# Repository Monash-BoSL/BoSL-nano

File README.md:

# micro-BoSL
A micro version of the BoSL board

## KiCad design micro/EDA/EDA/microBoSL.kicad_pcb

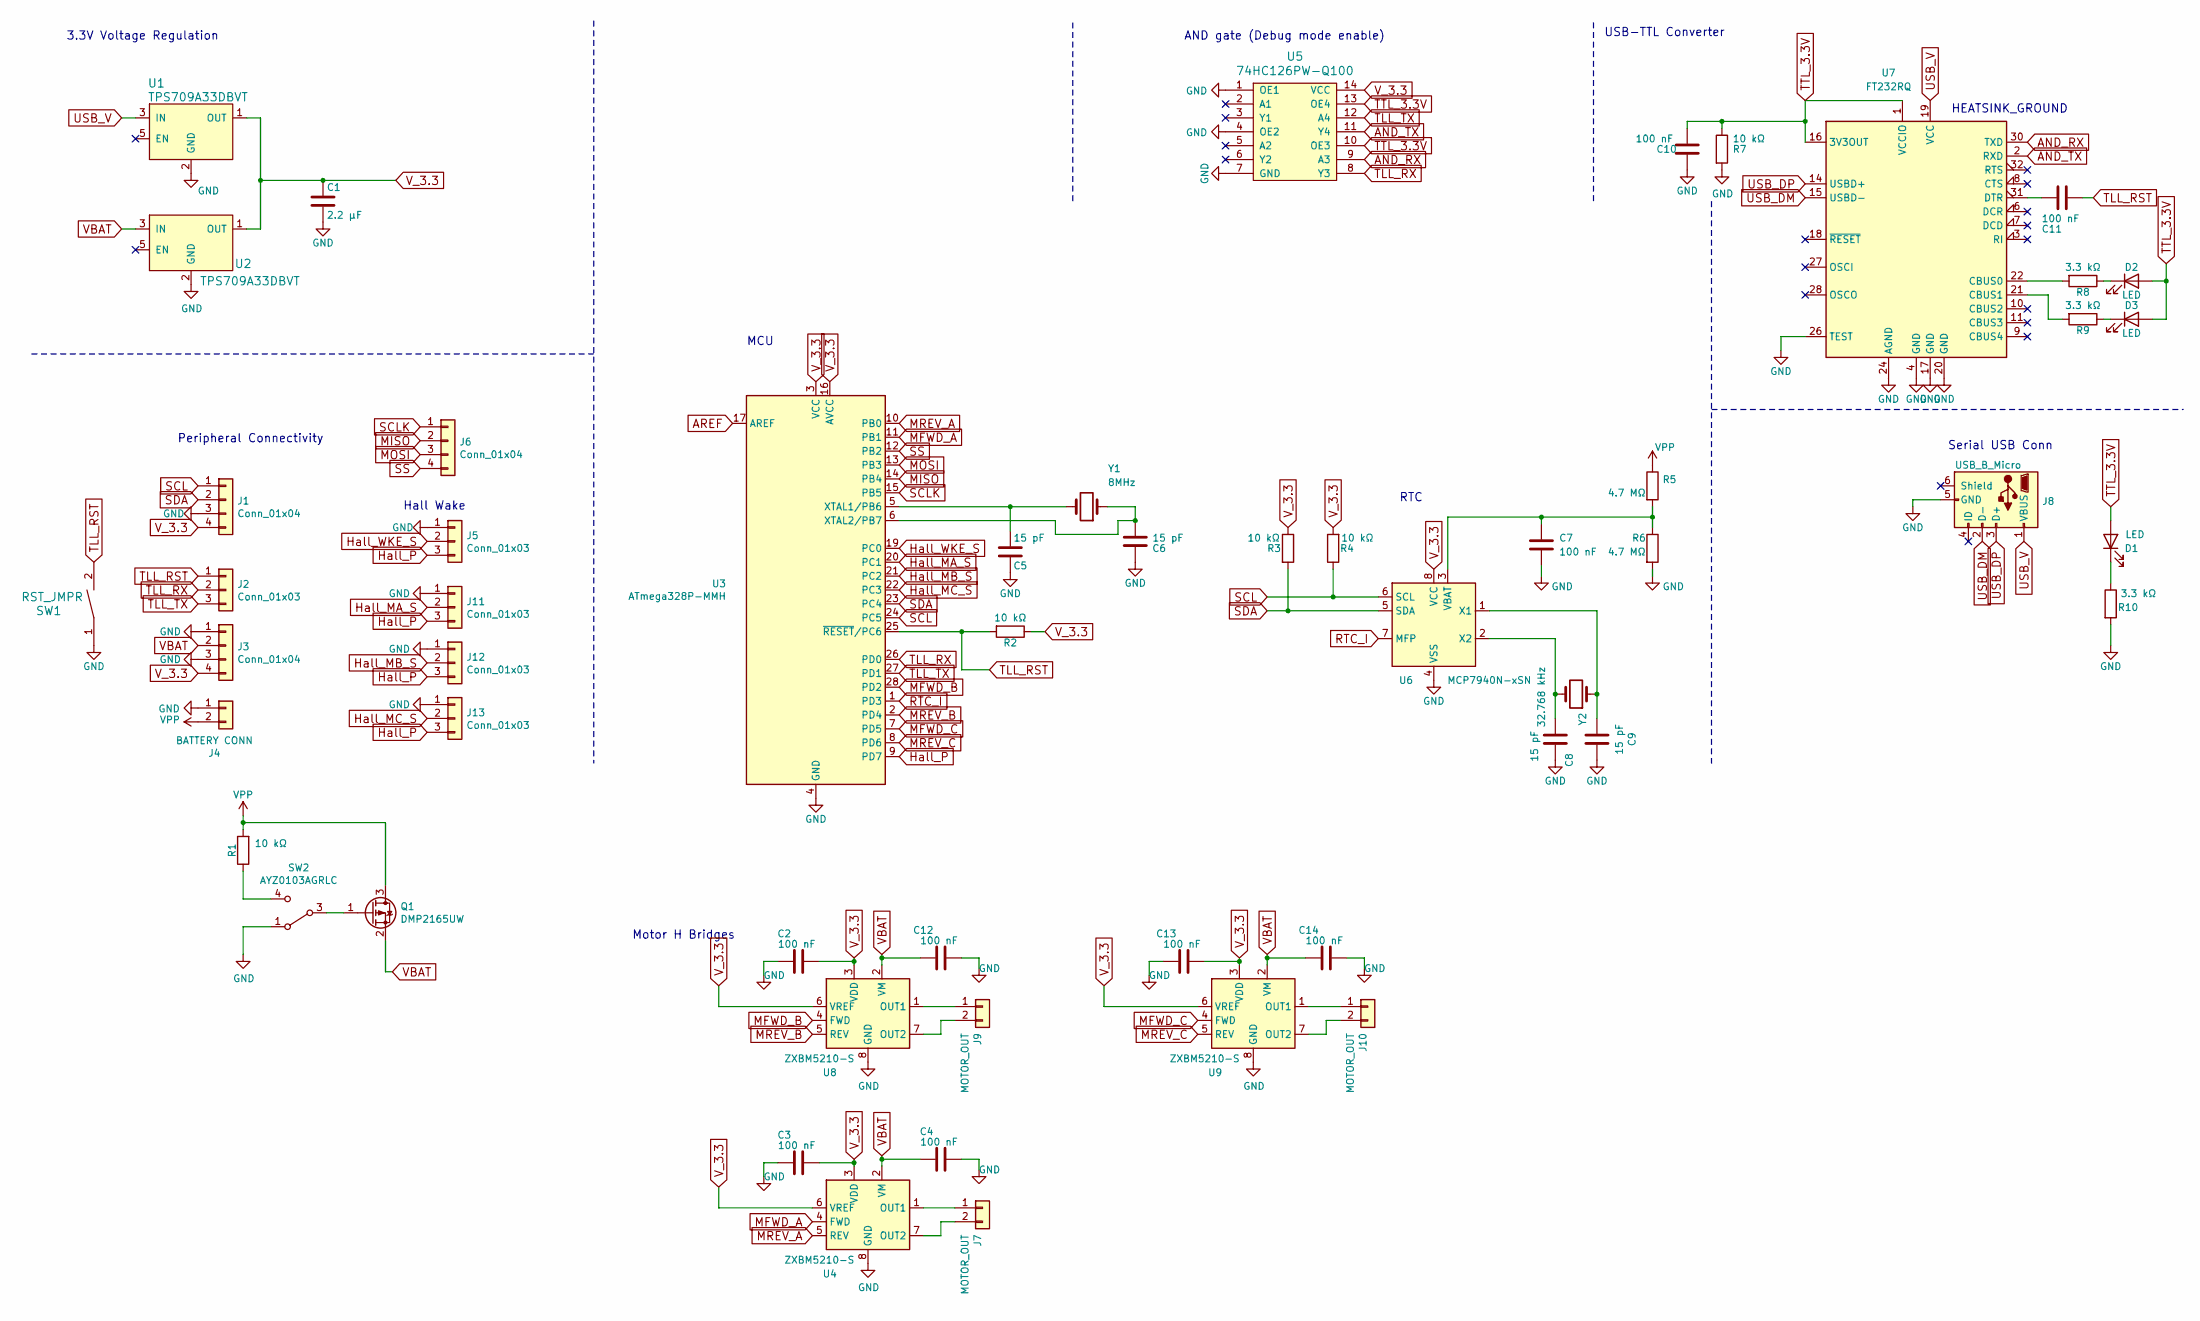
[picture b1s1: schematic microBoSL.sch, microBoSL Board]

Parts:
C1: 2.2 μF; C_0805_2012Metric
C2, C3, C4, C7, C10, C11, C12, C13, C14: 100 nF; C_0402_1005Metric
C5, C6, C8, C9: 15 pF; C_0402_1005Metric
D1, D2, D3: LED; LED_0603_1608Metric
J1, J6: Conn_01x04; PinHeader_1x04_P1.27mm_Vertical
J2: Conn_01x03; PinHeader_1x03_P1.27mm_Vertical
J3: Conn_01x04; PinHeader_1x04_P2.54mm_Vertical
J4: BATTERY CONN; PinHeader_1x02_P2.54mm_Vertical
J5, J11, J12, J13: Conn_01x03; PinHeader_1x03_P2.00mm_Vertical
J7, J9, J10: MOTOR_OUT; PinHeader_1x02_P2.54mm_Vertical
J8: USB_B_Micro; USB_Micro-B_Molex-105133-0001
Q1: DMP2165UW; SOT-323_SC-70
R1, R2, R3, R4, R7: 10 kΩ; R_0402_1005Metric
R5, R6: 4.7 MΩ; C_0402_1005Metric
R8, R9, R10: 3.3 kΩ; R_0402_1005Metric
SW1: RST_JMPR; SolderJumper-2_P1.3mm_Open_RoundedPad1.0x1.5mm
SW2: AYZ0103AGRLC
U1, U2: TPS709A33DBVT; SOT-23-5
U3: ATmega328P-MMH; QFN-28-1EP_4x4mm_P0.45mm_EP2.4x2.4mm
U4, U8, U9: ZXBM5210-S; SOIC-8_3.9x4.9mm_P1.27mm
U5: 74HC126PW-Q100; TSSOP-14_4.4x5mm_P0.65mm
U6: MCP7940N-xSN; DFN-8-1EP_3x2mm_P0.5mm_EP1.3x1.5mm
U7: FT232RQ; QFN-32-1EP_5x5mm_P0.5mm_EP3.1x3.1mm
Y1: 8MHz; Crystal_SMD_5032-2Pin_5.0x3.2mm
Y2: 32.768 kHz; Crystal_SMD_2012-2Pin_2.0x1.2mm

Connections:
AND_RX: U5.9 (A3), U7.30 (TXD)
AND_TX: U5.11 (Y4), U7.2 (RXD)
AREF: U3.17 (AREF)
GND: C1.2, C2.1, C3.1, C4.2, C5.1, C6.1, C7.2, C8.1, C9.1, C10.2, C12.2, C13.1, C14.2, J1.3, J3.1, J3.3, J4.1, J5.1, J8.5 (GND), J11.1, J12.1, J13.1, R6.2, R7.2, R10.2, SW1.1, SW2.1 (A), U1.2 (GND), U2.2 (GND), U3.4 (GND), U3.18 (GND), U3.29 (GND), U4.8 (GND), U5.1 (OE1), U5.4 (OE2), U5.7 (GND), U6.4 (VSS), U7.4 (GND), U7.17 (GND), U7.20 (GND), U7.24 (AGND), U7.26 (TEST), U7.33, U8.8 (GND), U9.8 (GND); also elsewhere on the board
Hall_MA_S: J11.2, U3.20 (PC1)
Hall_MB_S: J12.2, U3.21 (PC2)
Hall_MC_S: J13.2, U3.22 (PC3)
Hall_P: J5.3, J11.3, J12.3, J13.3, U3.9 (PD7)
Hall_WKE_S: J5.2, U3.19 (PC0)
MFWD_A: U3.11 (PB1), U4.4 (FWD)
MFWD_B: U3.28 (PD2), U8.4 (FWD)
MFWD_C: U3.7 (PD5), U9.4 (FWD)
MISO: J6.2, U3.14 (PB4)
MOSI: J6.3, U3.13 (PB3)
MREV_A: U3.10 (PB0), U4.5 (REV)
MREV_B: U3.2 (PD4), U8.5 (REV)
MREV_C: U3.8 (PD6), U9.5 (REV)
unnamed: C5.2, U3.5 (XTAL1/PB6), Y1.2
unnamed: C6.2, U3.6 (XTAL2/PB7), Y1.1
unnamed: C7.1, R5.2, R6.1, U6.3 (VBAT)
unnamed: C8.2, U6.2 (X2), Y2.2
unnamed: C9.2, U6.1 (X1), Y2.1
unnamed: C11.2, U7.31 (DTR)
unnamed: D1.1 (K), R10.1
unnamed: D2.1 (K), R8.1
unnamed: D3.1 (K), R9.1
unnamed: J7.1, U4.1 (OUT1)
unnamed: J7.2, U4.7 (OUT2)
unnamed: J9.1, U8.1 (OUT1)
unnamed: J9.2, U8.7 (OUT2)
unnamed: J10.1, U9.1 (OUT1)
unnamed: J10.2, U9.7 (OUT2)
unnamed: Q1.1 (G), SW2.3 (B)
unnamed: R1.1, SW2.4 (C)
unnamed: R8.2, U7.22 (CBUS0)
unnamed: R9.2, U7.21 (CBUS1)
RTC_I: U3.1 (PD3), U6.7 (MFP)
SCL: J1.1, R4.1, U3.24 (PC5), U6.6 (SCL)
SCLK: J6.1, U3.15 (PB5)
SDA: J1.2, R3.2, U3.23 (PC4), U6.5 (SDA)
SS: J6.4, U3.12 (PB2)
TLL_RST: C11.1, J2.1, R2.2, SW1.2, U3.25 (~RESET~/PC6); also elsewhere on the board
TLL_RX: J2.2, U3.26 (PD0), U5.8 (Y3)
TLL_TX: J2.3, U3.27 (PD1), U5.12 (A4)
TTL_3.3V: C10.1, D1.2 (A), D2.2 (A), D3.2 (A), R7.1, U5.10 (OE3), U5.13 (OE4), U7.1 (VCCIO), U7.16 (3V3OUT)
USB_DM: J8.2 (D-), U7.15 (USBD-)
USB_DP: J8.3 (D+), U7.14 (USBD+)
USB_V: J8.1 (VBUS), U1.3 (IN), U7.19 (VCC)
VBAT: C4.1, C12.1, C14.1, J3.2, Q1.2 (S), U2.3 (IN), U4.2 (VM), U8.2 (VM), U9.2 (VM)
VPP: J4.2, Q1.3 (D), R1.2, R5.1
V_3.3: C1.1, C2.2, C3.2, C13.2, J1.4, J3.4, R2.1, R3.1, R4.2, U1.1 (OUT), U2.1 (OUT), U3.3 (VCC), U3.16 (AVCC), U4.3 (VDD), U4.6 (VREF), U5.14 (VCC), U6.8 (VCC), U8.3 (VDD), U8.6 (VREF), U9.3 (VDD), U9.6 (VREF)

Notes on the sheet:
3.3V Voltage Regulation
Peripheral Connectivity
RTC
Hall Wake
HEATSINK_GROUND
USB-TTL Converter
AND gate (Debug mode enable)
Serial USB Conn
MCU
Motor H Bridges

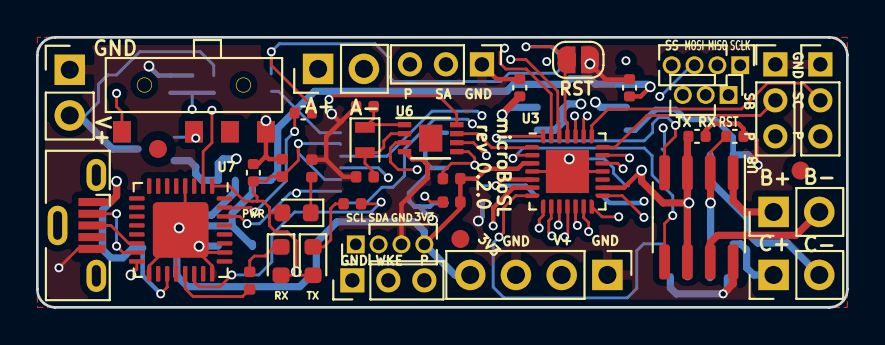
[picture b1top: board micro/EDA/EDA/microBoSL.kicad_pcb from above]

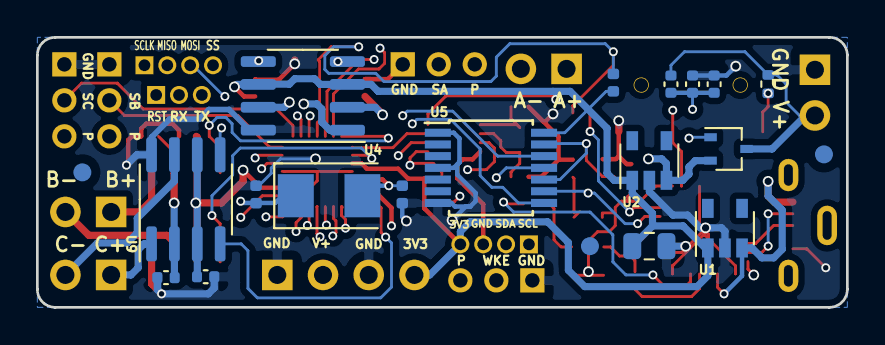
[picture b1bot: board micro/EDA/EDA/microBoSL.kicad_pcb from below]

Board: 4 copper layers, 45.0 x 15.0 mm, 54 parts (17 on the bottom side), 50 nets.

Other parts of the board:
RST: RST_JMPR; SolderJumper-2_P1.3mm_Open_RoundedPad1.0x1.5mm

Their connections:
GND: RST.1; also elsewhere on the board
TLL_RST: RST.2; also elsewhere on the board

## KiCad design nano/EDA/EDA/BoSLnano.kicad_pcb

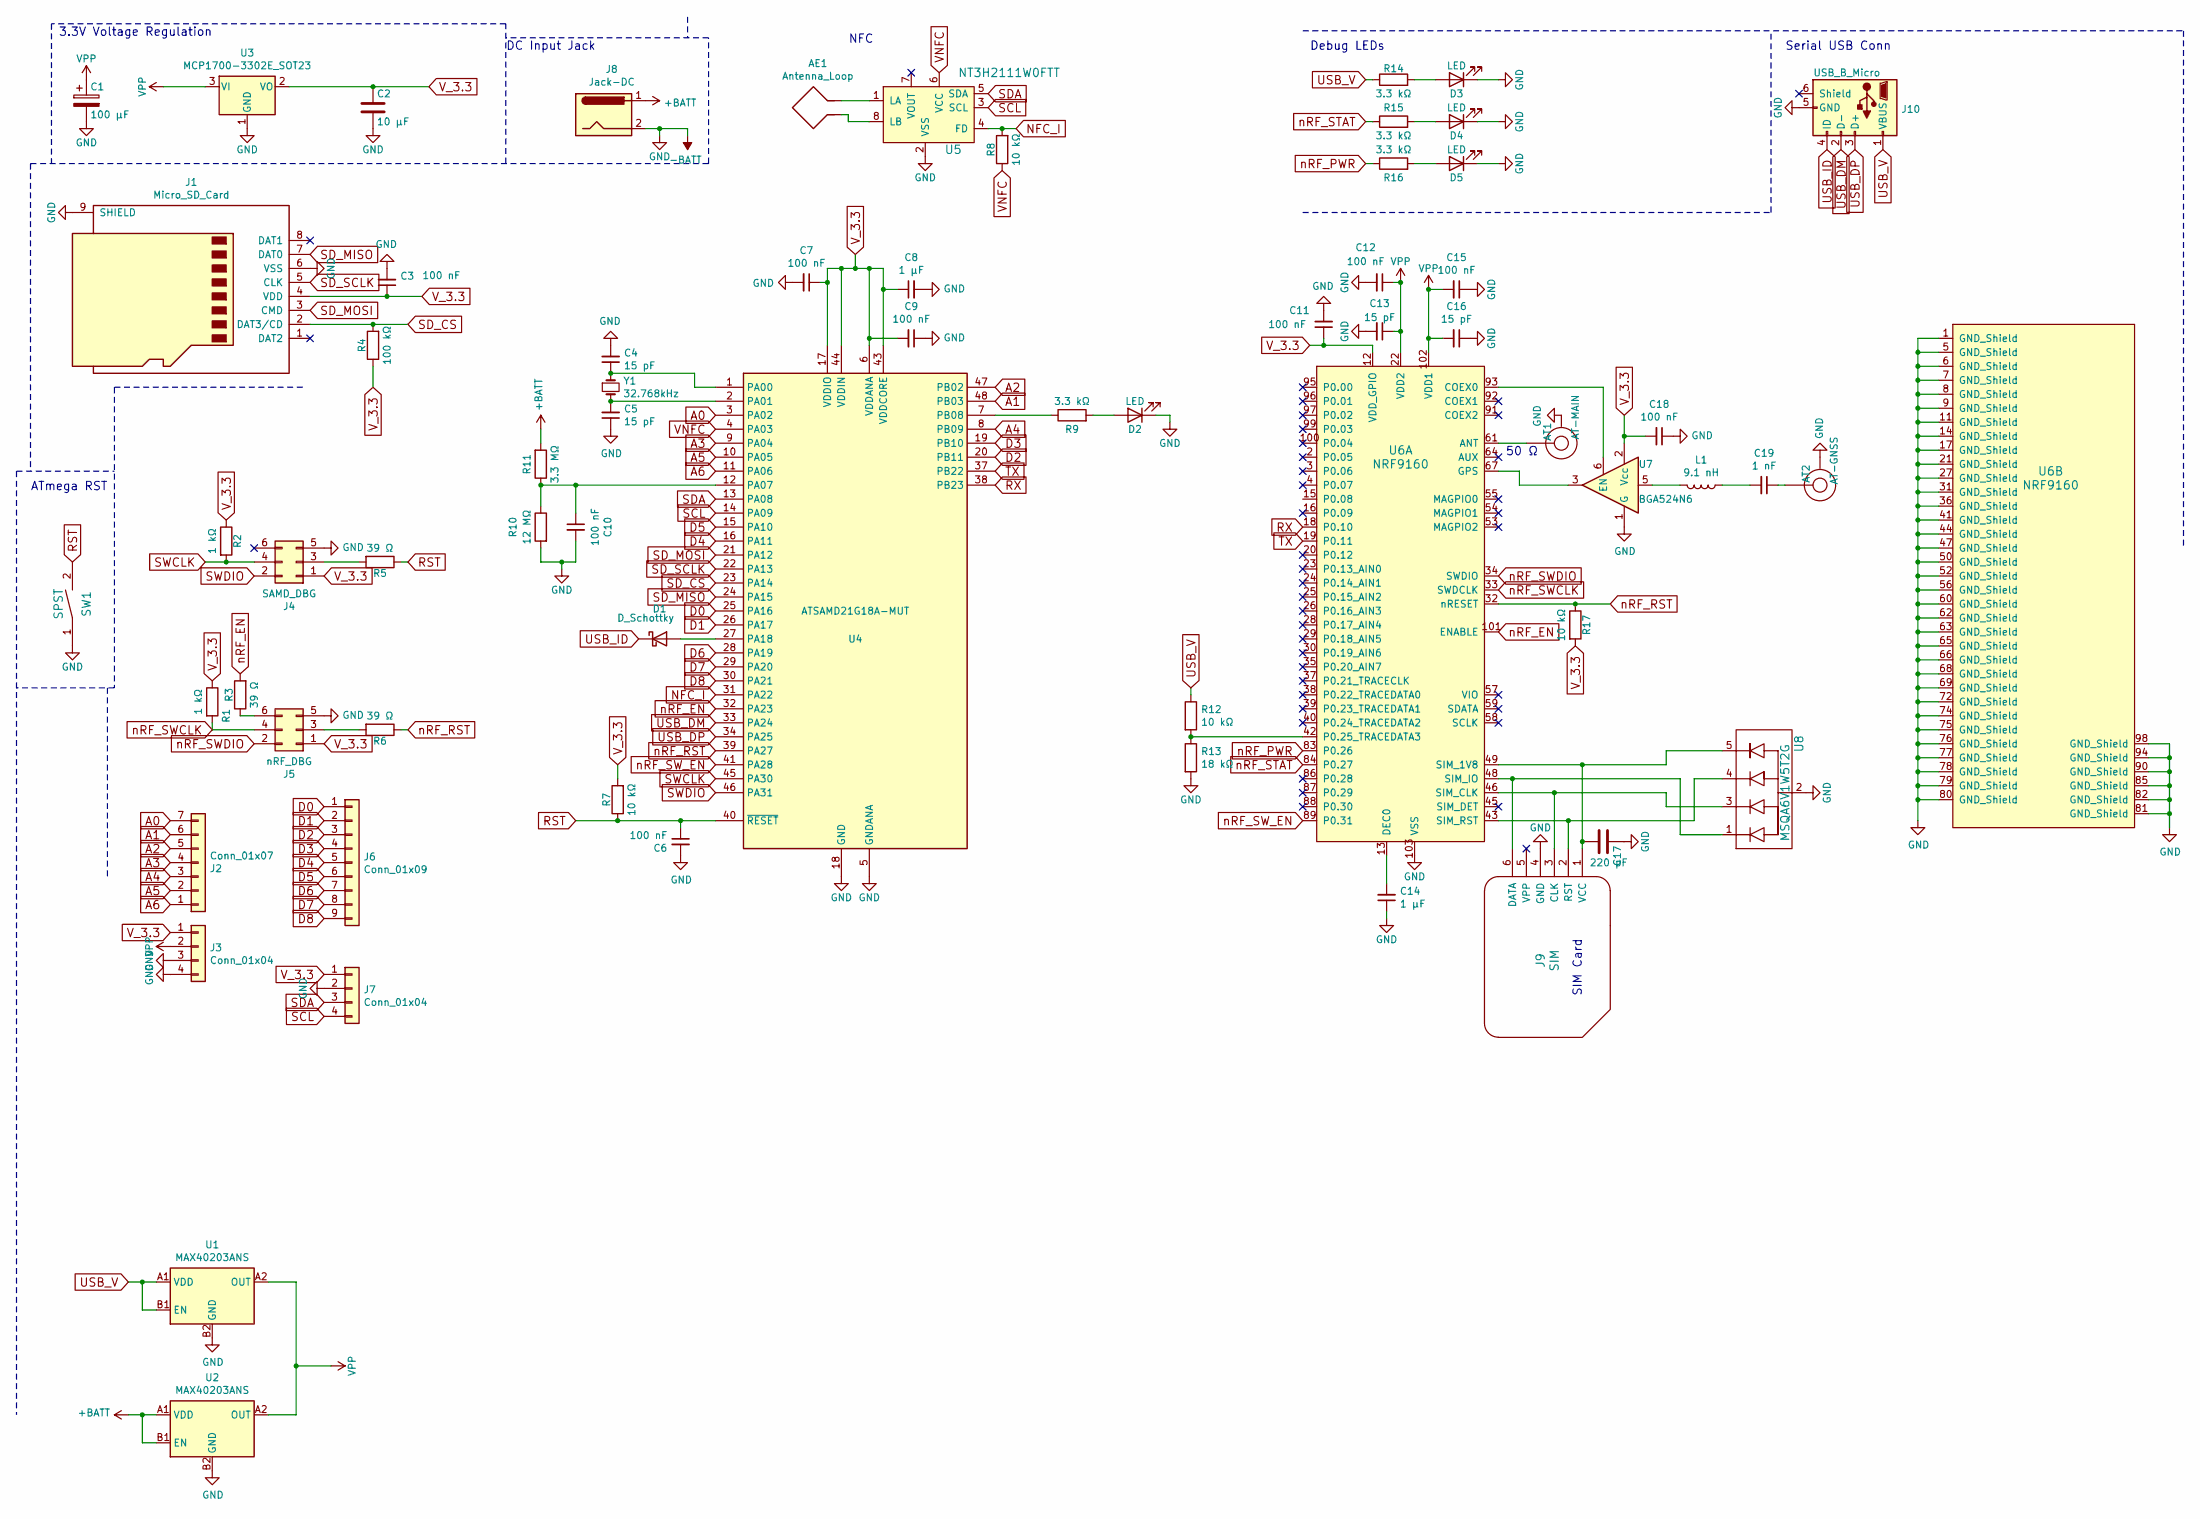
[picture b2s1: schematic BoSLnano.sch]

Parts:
AE1: Antenna_Loop; NFC antenna
AT1: AT-MAIN; U.FL_Molex_MCRF_73412-0110_Vertical
AT2: AT-GNSS; U.FL_Molex_MCRF_73412-0110_Vertical
C1: 100 μF; CP_Elec_5x5.8
C2: 10 μF; C_0805_2012Metric
C3, C6, C7, C9, C10, C11, C12, C15, C18: 100 nF; C_0402_1005Metric
C4, C5, C13, C16: 15 pF; C_0402_1005Metric
C8, C14: 1 μF; C_0402_1005Metric
C17: 220 pF; C_0402_1005Metric
C19: 1 nF; C_0402_1005Metric
D1: D_Schottky; SOD882
D2, D3, D4, D5: LED; LED_0603_1608Metric
J1: Micro_SD_Card; microSD_Connector
J2: Conn_01x07; PinHeader_1x07_P2.54mm_Vertical
J3, J7: Conn_01x04; PinHeader_1x04_P2.54mm_Vertical
J4: SAMD_DBG; TC2030_Pinless
J5: nRF_DBG; TC2030_Pinless
J6: Conn_01x09; PinHeader_1x09_P1.27mm_Vertical
J8: Jack-DC; JST_PH_S2B-PH-SM4-TB_1x02-1MP_P2.00mm_Horizontal
J9: SIM; SIMNano
J10: USB_B_Micro; USB_Micro-B_Molex-105133-0001
L1: 9.1 nH; L_0603_1608Metric
R1, R2: 1 kΩ; R_0402_1005Metric
R3, R5, R6: 39 Ω; R_0402_1005Metric
R4: 100 kΩ; R_0402_1005Metric
R7, R8, R12, R17: 10 kΩ; R_0402_1005Metric
R9, R14, R15, R16: 3.3 kΩ; R_0402_1005Metric
R10: 12 MΩ; R_0402_1005Metric
R11: 3.3 MΩ; R_0402_1005Metric
R13: 18 kΩ; R_0402_1005Metric
SW1: SPST; SW_Push_SPST_NO_Alps_SKRK
U1, U2: MAX40203ANS; WLP-4_0.73x0.73mm_Layout2x2_P0.35mm_Ball0.22mm_Pad0.2mm_NSMD
U3: MCP1700-3302E_SOT23; SOT-23
U4: ATSAMD21G18A-MUT; QFN-48-1EP_7x7mm_P0.5mm_EP5.15x5.15mm
U5: NT3H2111W0FTT; TSSOP-8_3x3mm_P0.65mm
U6: NRF9160; nRF9160
U7: BGA524N6; TSNP-6-2
U8: MSQA6V1W5T2G; SOT-353_SC-70-5
Y1: 32.768kHz; Crystal_SMD_EuroQuartz_EQ161-2Pin_3.2x1.5mm

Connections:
+BATT: J8.1, R11.2, U2.A1 (VDD), U2.B1 (EN)
-BATT: AT1.2, AT2.2, C1.2, C2.2, C3.2, C4.2, C5.1, C6.2, C7.2, C8.2, C9.1, C10.2, C11.2, C12.2, C13.2, C14.1, C15.1, C16.1, C17.1, C18.1, D2.1 (K), D3.1 (K), D4.1 (K), D5.1 (K), J1.6 (VSS), J1.9 (SHIELD), J3.3, J3.4, J4.5, J5.5, J7.2, J8.2, J9.4 (GND), J10.5 (GND), R10.2, R13.2, SW1.1, U1.B2 (GND), U2.B2 (GND), U3.1 (GND), U4.5 (GNDANA), U4.18 (GND), U4.35 (GND), U4.42 (GND), U4.49, U5.2 (VSS), U6.1 (GND_Shield), U6.5 (GND_Shield), U6.6 (GND_Shield), U6.7 (GND_Shield), U6.8 (GND_Shield), U6.9 (GND_Shield), U6.11 (GND_Shield), U6.14 (GND_Shield), U6.17 (GND_Shield), U6.21 (GND_Shield), U6.27 (GND_Shield), U6.31 (GND_Shield), U6.36 (GND_Shield), U6.41 (GND_Shield), U6.44 (GND_Shield), U6.47 (GND_Shield), U6.50 (GND_Shield), U6.52 (GND_Shield), U6.56 (GND_Shield), U6.60 (GND_Shield), U6.62 (GND_Shield), U6.63 (GND_Shield), U6.65 (GND_Shield), U6.66 (GND_Shield), U6.68 (GND_Shield), U6.69 (GND_Shield), U6.72 (GND_Shield), U6.74 (GND_Shield), U6.75 (GND_Shield), U6.76 (GND_Shield), U6.77 (GND_Shield), U6.78 (GND_Shield), U6.79 (GND_Shield), U6.80 (GND_Shield), U6.81 (GND_Shield), U6.82 (GND_Shield), U6.85 (GND_Shield), U6.90 (GND_Shield), U6.94 (GND_Shield), U6.98 (GND_Shield), U6.103 (VSS), U7.1 (G), U7.4 (G), U8.2
A0: J2.7, U4.3 (PA02)
A1: J2.6, U4.48 (PB03)
A2: J2.5, U4.47 (PB02)
A3: J2.4, U4.9 (PA04)
A4: J2.3, U4.8 (PB09)
A5: J2.2, U4.10 (PA05)
A6: J2.1, U4.11 (PA06)
D0: J6.1, U4.25 (PA16)
D1: J6.2, U4.26 (PA17)
D2: J6.3, U4.20 (PB11)
D3: J6.4, U4.19 (PB10)
D4: J6.5, U4.16 (PA11)
D5: J6.6, U4.15 (PA10)
D6: J6.7, U4.28 (PA19)
D7: J6.8, U4.29 (PA20)
D8: J6.9, U4.30 (PA21)
NFC_I: R8.2, U4.31 (PA22), U5.4 (FD)
unnamed: AE1.1, U5.8 (LB)
unnamed: AE1.2, U5.1 (LA)
unnamed: AT1.1, U6.61 (ANT)
unnamed: AT2.1, C19.1
unnamed: C4.1, U4.1 (PA00), Y1.1
unnamed: C5.2, U4.2 (PA01), Y1.2
unnamed: C10.1, R10.1, R11.1, U4.12 (PA07)
unnamed: C14.2, U6.13 (DEC0)
unnamed: C17.2, J9.1 (VCC), U6.49 (SIM_1V8), U8.5
unnamed: C19.2, L1.1
unnamed: D1.2 (A), U4.27 (PA18)
unnamed: D2.2 (A), R9.2
unnamed: D3.2 (A), R14.2
unnamed: D4.2 (A), R15.2
unnamed: D5.2 (A), R16.2
unnamed: J4.3, R5.2
unnamed: J5.3, R6.2
unnamed: J5.6, R3.1
unnamed: J9.2 (RST), U6.43 (SIM_RST), U8.4
unnamed: J9.3 (CLK), U6.46 (SIM_CLK), U8.3
unnamed: J9.6 (DATA), U6.48 (SIM_IO), U8.1
unnamed: L1.2, U7.5
unnamed: R9.1, U4.7 (PB08)
unnamed: R12.2, R13.1, U6.42 (P0.25_TRACEDATA3)
unnamed: U6.67 (GPS), U7.3
unnamed: U6.93 (COEX0), U7.6 (EN)
RST: C6.1, R5.1, R7.1, SW1.2, U4.40 (~RESET)
RX: U4.38 (PB23), U6.18 (P0.10)
SCL: J7.4, U4.14 (PA09), U5.3 (SCL)
SDA: J7.3, U4.13 (PA08), U5.5 (SDA)
SD_CS: J1.2 (DAT3/CD), R4.2, U4.23 (PA14)
SD_MISO: J1.7 (DAT0), U4.24 (PA15)
SD_MOSI: J1.3 (CMD), U4.21 (PA12)
SD_SCLK: J1.5 (CLK), U4.22 (PA13)
SWCLK: J4.4, R2.2, U4.45 (PA30)
SWDIO: J4.2, U4.46 (PA31)
TX: U4.37 (PB22), U6.19 (P0.11)
USB_DM: J10.2 (D-), U4.33 (PA24)
USB_DP: J10.3 (D+), U4.34 (PA25)
USB_ID: D1.1 (K), J10.4 (ID)
USB_V: J10.1 (VBUS), R12.1, R14.1, U1.A1 (VDD), U1.B1 (EN)
VNFC: R8.1, U4.4 (PA03), U5.6 (VCC)
VPP: C1.1, C12.1, C13.1, C15.2, C16.2, J3.2, U1.A2 (OUT), U2.A2 (OUT), U3.3 (VI), U6.22 (VDD2), U6.102 (VDD1)
V_3.3: C2.1, C3.1, C7.1, C8.1, C9.2, C11.1, C18.2, J1.4 (VDD), J3.1, J4.1, J5.1, J7.1, R1.1, R2.1, R4.1, R7.2, R17.2, U3.2 (VO), U4.6 (VDDANA), U4.17 (VDDIO), U4.36 (VDDIO), U4.43 (VDDCORE), U4.44 (VDDIN), U6.12 (VDD_GPIO), U7.2 (Vcc)
nRF_EN: R3.2, U4.32 (PA23), U6.101 (ENABLE)
nRF_PWR: R16.1, U6.83 (P0.26)
nRF_RST: R6.1, R17.1, U4.39 (PA27), U6.32 (nRESET)
nRF_STAT: R15.1, U6.84 (P0.27)
nRF_SWCLK: J5.4, R1.2, U6.33 (SWDCLK)
nRF_SWDIO: J5.2, U6.34 (SWDIO)
nRF_SW_EN: U4.41 (PA28), U6.89 (P0.31)

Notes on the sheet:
3.3V Voltage Regulation
DC Input Jack
SIM Card
Debug LEDs
NFC
Serial USB Conn
50 Ω
ATmega RST

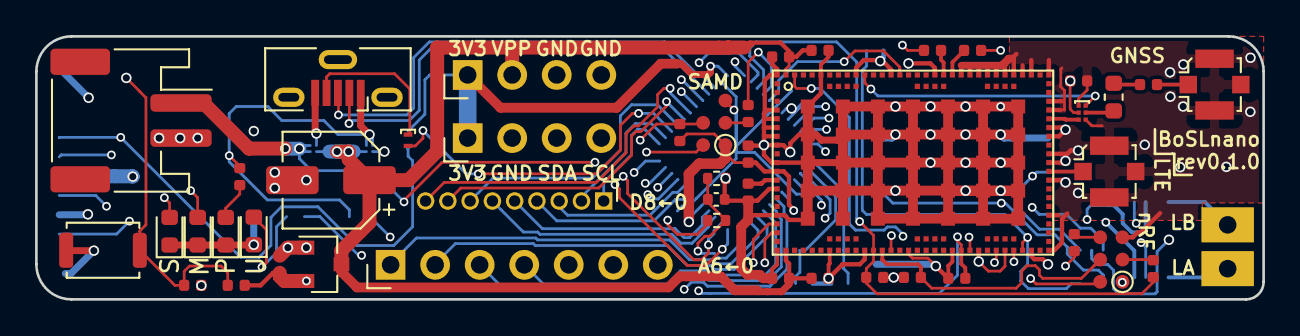
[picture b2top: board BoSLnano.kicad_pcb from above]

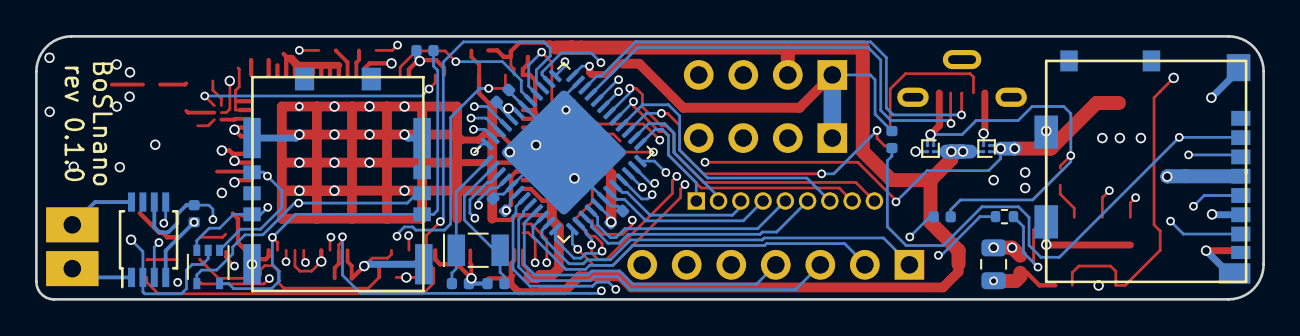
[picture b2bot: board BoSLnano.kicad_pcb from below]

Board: 4 copper layers, 70.0 x 15.0 mm, 65 parts (19 on the bottom side), 70 nets.

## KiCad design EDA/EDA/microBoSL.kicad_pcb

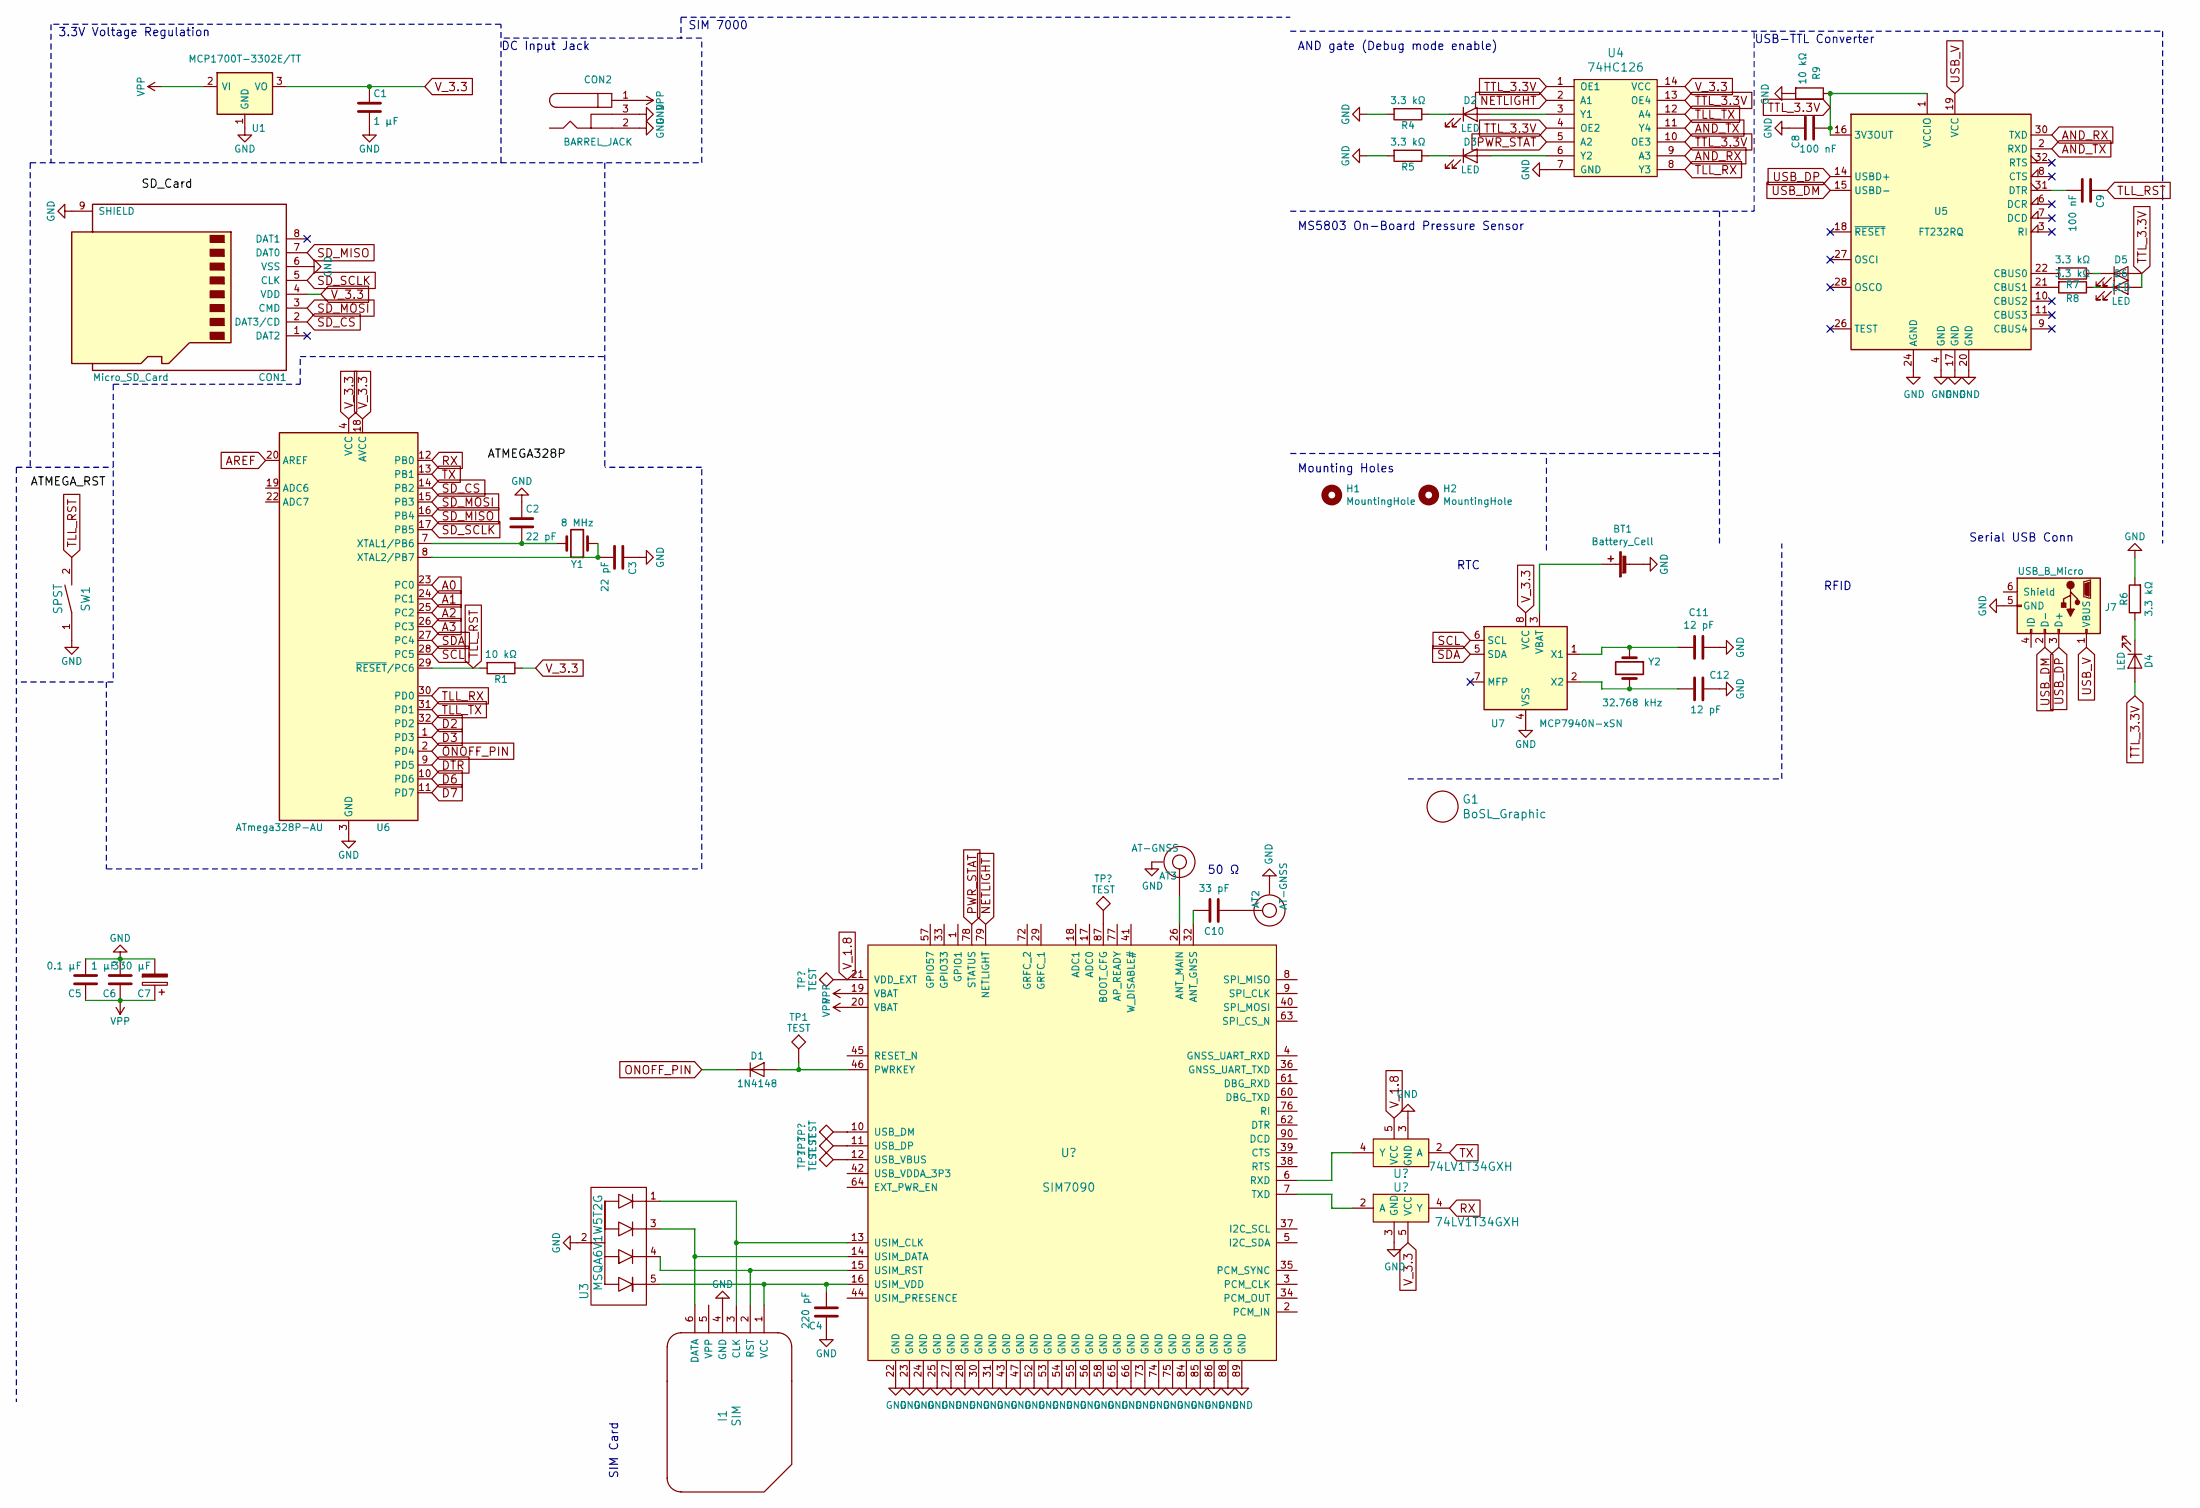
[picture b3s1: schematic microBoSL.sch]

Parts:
AT2, AT3: AT-GNSS; U.FL_Molex_MCRF_73412-0110_Vertical
BT1: Battery_Cell; 2996TR
C1, C6: 1 μF; C_1206_3216Metric
C2, C3: 22 pF; C_0603_1608Metric
C4: 220 pF; C_0603_1608Metric
C5: 0.1 μF; C_0805_2012Metric
C7: 330 μF; CP_Elec_8x10
C8, C9: 100 nF; C_0603_1608Metric
C10: 33 pF; C_0603_1608Metric
C11, C12: 12 pF; C_0603_1608Metric
CON1: Micro_SD_Card; microSD_Connector
CON2: BARREL_JACK; BarrelJack_Horizontal
D1: 1N4148; D_SOD-323
D2, D3, D4, D5, D6: LED; LED_0603_1608Metric
G1: BoSL_Graphic
H1, H2: MountingHole; MountingHole_2.2mm_M2_Pad
I1: SIM; SIMNano
J7: USB_B_Micro; USB_Micro-B_Molex-105133-0001
R1, R9: 10 kΩ; R_0603_1608Metric
R4, R5, R6, R7, R8: 3.3 kΩ; R_0603_1608Metric
SW1: SPST; SW_SPST_B3S-1000
TP1: TEST; TestPoint_Pad_D1.0mm
U1: MCP1700T-3302E/TT; SOT-89-3
U3: MSQA6V1W5T2G; SOT-353_SC-70-5
U4: 74HC126; TSSOP-14_4.4x5mm_P0.65mm
U5: FT232RQ; QFN-32-1EP_5x5mm_P0.5mm_EP3.1x3.1mm
U6: ATmega328P-AU; QFN-32-1EP_5x5mm_P0.5mm_EP3.1x3.1mm
U7: MCP7940N-xSN; DFN-8-1EP_3x2mm_P0.5mm_EP1.3x1.5mm
Y1: 8 MHz; Crystal_SMD_5032-2Pin_5.0x3.2mm
Y2: 32.768 kHz; Crystal_SMD_EuroQuartz_EQ161-2Pin_3.2x1.5mm

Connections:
A0: U6.23 (PC0)
A1: U6.24 (PC1)
A2: U6.25 (PC2)
A3: U6.26 (PC3)
AND_RX: U4.9 (A3), U5.30 (TXD)
AND_TX: U4.11 (Y4), U5.2 (RXD)
AREF: U6.20 (AREF)
D2: U6.32 (PD2)
D3: U6.1 (PD3)
D6: U6.10 (PD6)
D7: U6.11 (PD7)
DTR: U6.9 (PD5)
GND: AT2.2, AT3.2, BT1.2 (-), C1.2, C2.1, C3.1, C4.1, C5.2, C6.2, C7.2, C8.1, C11.1, C12.1, CON1.6 (VSS), CON1.9 (SHIELD), CON2.2, CON2.3, I1.4 (GND), J7.5 (GND), R4.2, R5.2, R6.2, R9.2, SW1.1, U1.1 (GND), U3.2, U4.7 (GND), U5.4 (GND), U5.17 (GND), U5.20 (GND), U5.24 (AGND), U6.3 (GND), U6.5 (GND), U6.21 (GND), U7.4 (VSS)
NETLIGHT: U4.2 (A1)
unnamed: AT2.1, C10.1
unnamed: BT1.1 (+), U7.3 (VBAT)
unnamed: C2.2, U6.7 (XTAL1/PB6), Y1.2
unnamed: C3.2, U6.8 (XTAL2/PB7), Y1.1
unnamed: C4.2, I1.1 (VCC), U3.5
unnamed: C9.2, U5.31 (DTR)
unnamed: C11.2, U7.1 (X1), Y2.1
unnamed: C12.2, U7.2 (X2), Y2.2
unnamed: D1.2 (A), TP1.1
unnamed: D2.1 (K), R4.1
unnamed: D2.2 (A), U4.3 (Y1)
unnamed: D3.1 (K), R5.1
unnamed: D3.2 (A), U4.6 (Y2)
unnamed: D4.1 (K), R6.1
unnamed: D5.1 (K), R7.1
unnamed: D6.1 (K), R8.1
unnamed: I1.2 (RST), U3.4
unnamed: I1.3 (CLK), U3.1
unnamed: I1.6 (DATA), U3.3
unnamed: R7.2, U5.22 (CBUS0)
unnamed: R8.2, U5.21 (CBUS1)
ONOFF_PIN: D1.1 (K), U6.2 (PD4)
PWR_STAT: U4.5 (A2)
RX: U6.12 (PB0)
SCL: U6.28 (PC5), U7.6 (SCL)
SDA: U6.27 (PC4), U7.5 (SDA)
SD_CS: CON1.2 (DAT3/CD), U6.14 (PB2)
SD_MISO: CON1.7 (DAT0), U6.16 (PB4)
SD_MOSI: CON1.3 (CMD), U6.15 (PB3)
SD_SCLK: CON1.5 (CLK), U6.17 (PB5)
TLL_RST: C9.1, R1.2, SW1.2, U6.29 (~RESET~/PC6)
TLL_RX: U4.8 (Y3), U6.30 (PD0)
TLL_TX: U4.12 (A4), U6.31 (PD1)
TTL_3.3V: C8.2, D4.2 (A), D5.2 (A), D6.2 (A), R9.1, U4.1 (OE1), U4.4 (OE2), U4.10 (OE3), U4.13 (OE4), U5.1 (VCCIO), U5.16 (3V3OUT)
TX: U6.13 (PB1)
USB_DM: J7.2 (D-), U5.15 (USBD-)
USB_DP: J7.3 (D+), U5.14 (USBD+)
USB_V: J7.1 (VBUS), U5.19 (VCC)
VPP: C5.1, C6.1, C7.1, CON2.1, U1.2 (VI)
V_3.3: C1.1, CON1.4 (VDD), R1.1, U1.3 (VO), U4.14 (VCC), U6.4 (VCC), U6.6 (VCC), U6.18 (AVCC), U7.8 (VCC)

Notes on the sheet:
3.3V Voltage Regulation
DC Input Jack
SIM 7000
SIM Card
AND gate (Debug mode enable)
MS5803 On-Board Pressure Sensor
Mounting Holes
RTC
RFID
Serial USB Conn
USB-TTL Converter
50 Ω

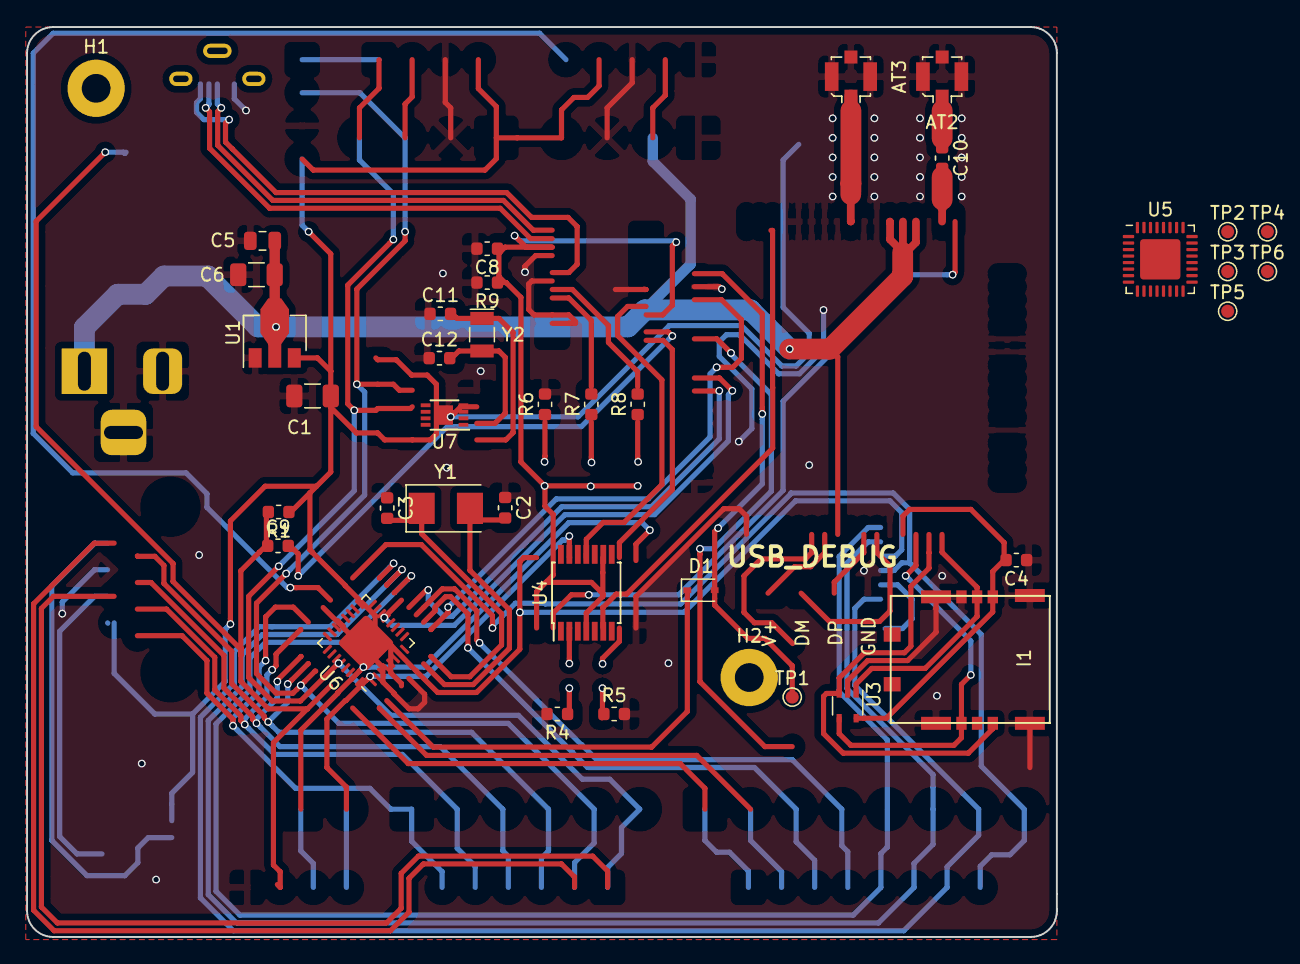
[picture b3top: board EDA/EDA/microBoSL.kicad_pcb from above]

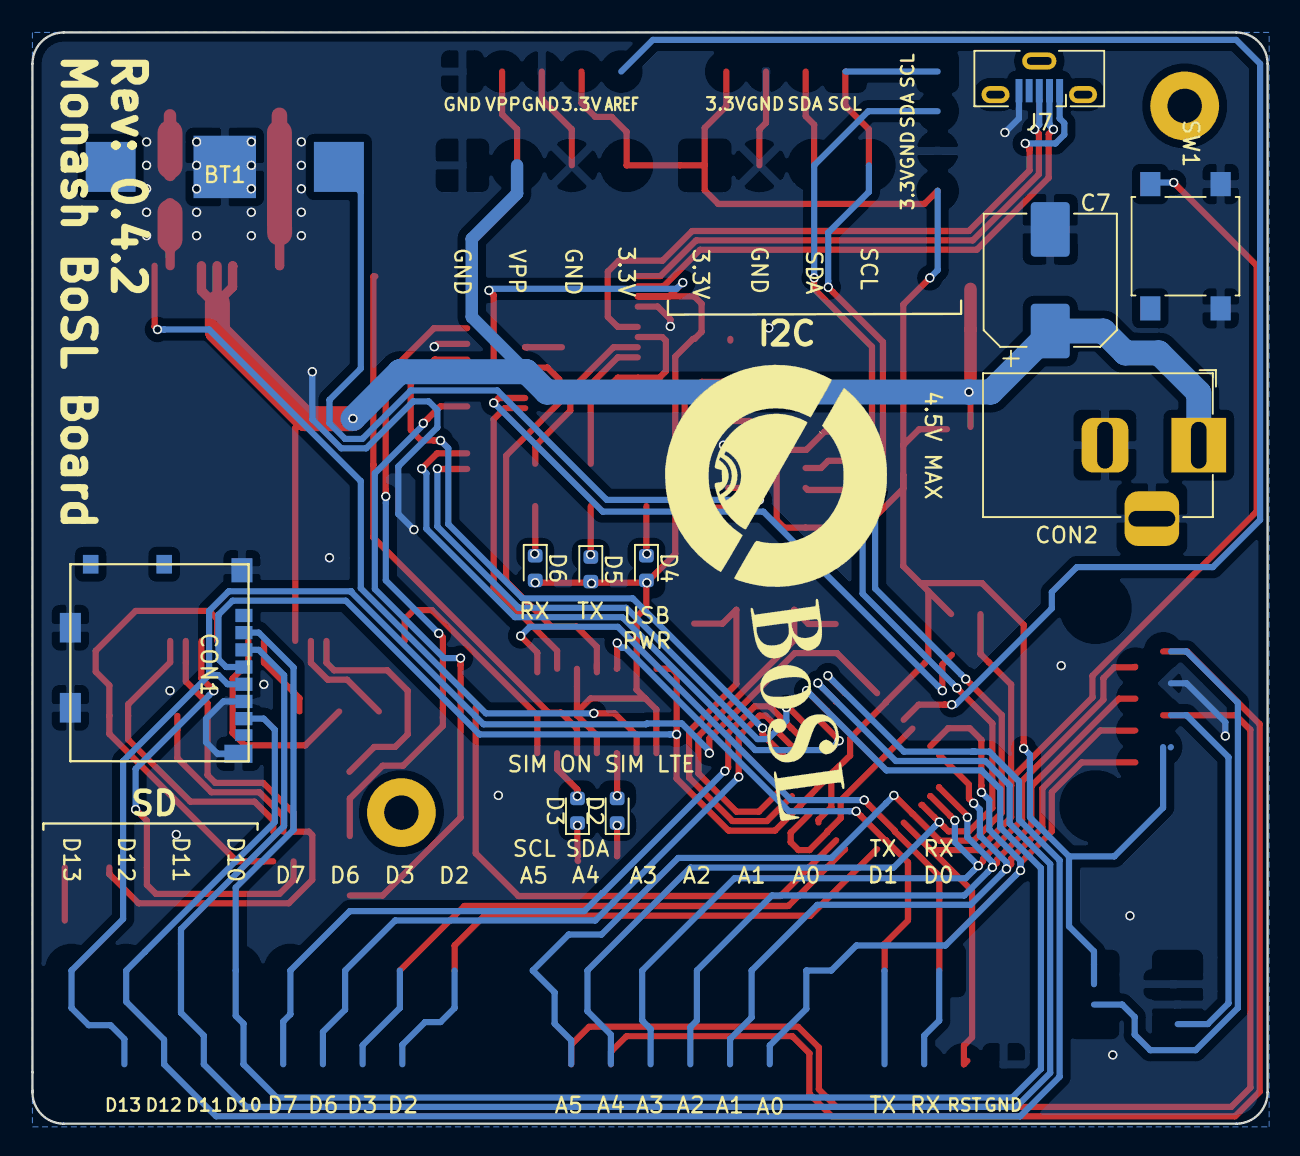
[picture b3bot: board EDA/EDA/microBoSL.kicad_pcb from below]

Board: 2 copper layers, 79.0 x 69.8 mm, 50 parts (12 on the bottom side), 40 nets.

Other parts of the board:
TP2, TP3, TP4, TP5, TP6: TEST; TestPoint_Pad_D1.0mm

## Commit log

2020-12-02 addded BoSL files
2020-12-02 chnaged a few packages arround
2020-12-03 added new footprints
2020-12-04 preliminary layout
2020-12-04 partial layout compactification
2020-12-07 finished layout of micro board
2020-12-08 finished micro bosl design
2020-12-08 changed some labled on microBoSL
2021-01-19 finished bom and schematic - nano
2021-01-21 added battery connector
2021-01-21 changed connectivity
2021-01-27 modifed nano
2021-01-28 made to be 70 mm
2021-01-29 began routing nano
2021-02-01 finished PCB layout
2021-02-28 added hardware documentation
2021-04-28 updated microbosl schematic
2021-04-29 worked on micro BOM
2021-05-03 finished BOM
2021-05-03 microbosl layout finished TODO: optimise/silkscreen
2021-05-03 optimised tracing on micro
2021-05-04 added silkscreen to microbosl
2021-05-07 added 3 motors to the microBoSL in schematic and PCB, traces and silkscreen still need optimising
2021-05-13 routed pcb with 4 hall effect sensors, TODO silkscreen
2021-05-14 micro traces optimised and silkscreened TODO: panelisation
2021-05-15 added panelisation and gerber for micro
2021-05-17 updated microBoSL panel with extra spacing
2021-05-19 modifed spacing on micro pcb panel
2021-06-24 fixed power switch on microBoSL added o-ring fix pinout
2021-06-24 moved microBoSL to seperate repository
